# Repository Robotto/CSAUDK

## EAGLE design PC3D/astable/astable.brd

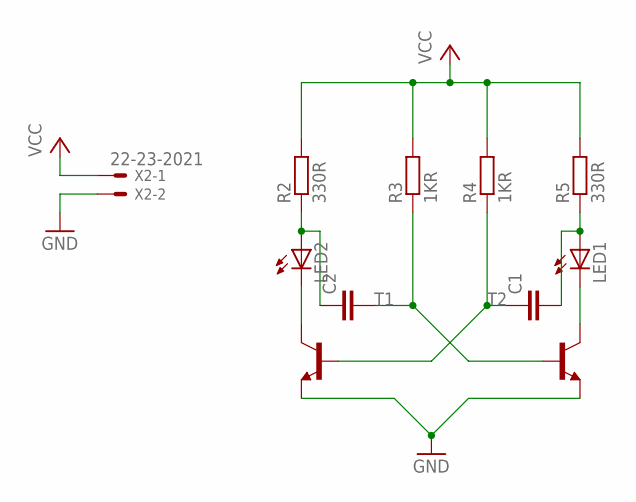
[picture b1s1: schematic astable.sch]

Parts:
C1, C2: C-EU025-030X050; C025-030X050
LED1, LED2: LED5MM
R2, R5: 330R; 0207/10
R3, R4: 1KR; 0207/10
T1, T2: -NPN-TO92-E1; TO92-E1
X2: 22-23-2021

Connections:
GND: T1.3 (E), T2.3 (E), X2.2
unnamed: C2.2, R3.1, T2.2 (B)
unnamed: C1.1, R4.1, T1.2 (B)
unnamed: C2.1, LED2.A, R2.1
unnamed: LED2.K (C), T1.1 (C)
unnamed: LED1.K (C), T2.1 (C)
unnamed: C1.2, LED1.A, R5.1
VCC: R2.2, R3.2, R4.2, R5.2, X2.1

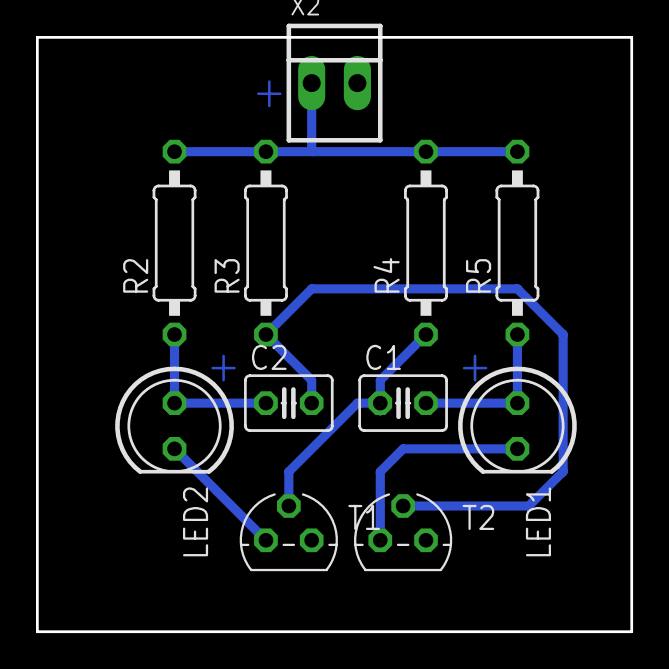
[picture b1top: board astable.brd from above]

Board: 2 copper layers, 33.0 x 33.0 mm, 11 parts (0 on the bottom side), 8 nets.

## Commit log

2017-08-08 init
2017-09-01 added astable multivibrator eagle files
